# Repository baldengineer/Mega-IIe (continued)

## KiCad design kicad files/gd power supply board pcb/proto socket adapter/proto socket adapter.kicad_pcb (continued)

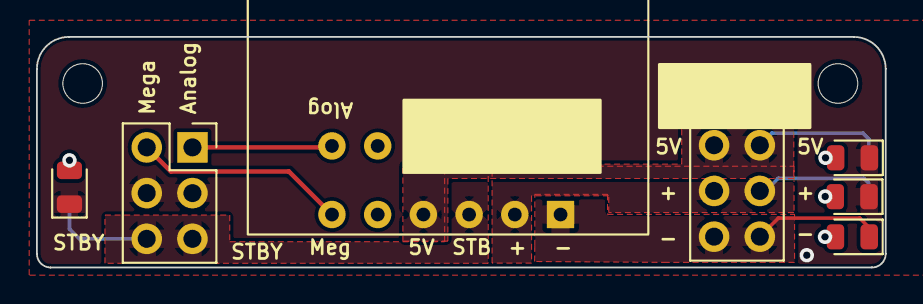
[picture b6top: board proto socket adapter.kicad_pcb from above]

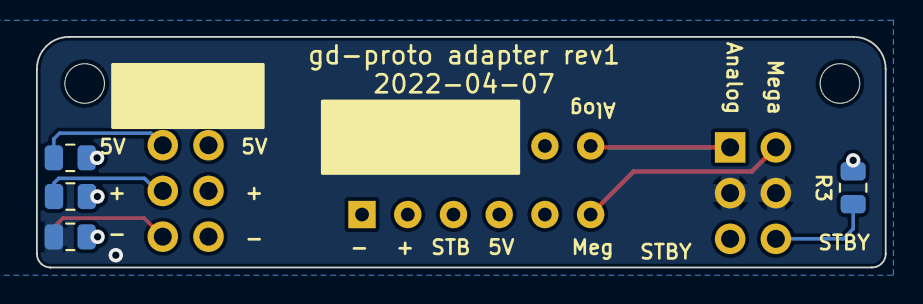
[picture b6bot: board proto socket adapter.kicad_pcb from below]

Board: 2 copper layers, 47.2 x 12.8 mm, 13 parts (4 on the bottom side), 11 nets.

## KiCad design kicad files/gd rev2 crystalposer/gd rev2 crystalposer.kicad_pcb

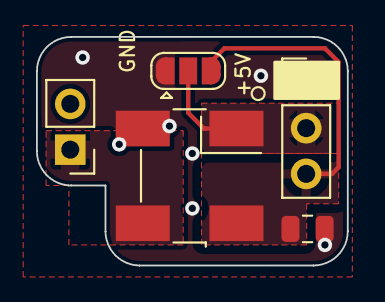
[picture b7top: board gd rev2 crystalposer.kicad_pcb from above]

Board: 2 copper layers, 17.3 x 12.7 mm, 5 parts (0 on the bottom side), 4 nets.

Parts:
C1: 1uF; C_0805_2012Metric
J1: 14M Enable; PinHeader_1x03_P2.54mm_Vertical
J2: 14M_SEL; PinHeader_1x02_P2.54mm_Vertical
JP1: X_EN; SolderJumper-3_P1.3mm_Open_RoundedPad1.0x1.5mm
X1: 14.31818MHz; Oscillator_MCP_SMD_7050

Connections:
+5V: C1.1, J1.3, JP1.3 (B), X1.4 (V+)
/14M: J2.1, X1.3 (OUT)
/EN: J1.2, JP1.2 (C), X1.1 (EN)
GND: C1.2, J1.1, JP1.1 (A), X1.2 (GND)
